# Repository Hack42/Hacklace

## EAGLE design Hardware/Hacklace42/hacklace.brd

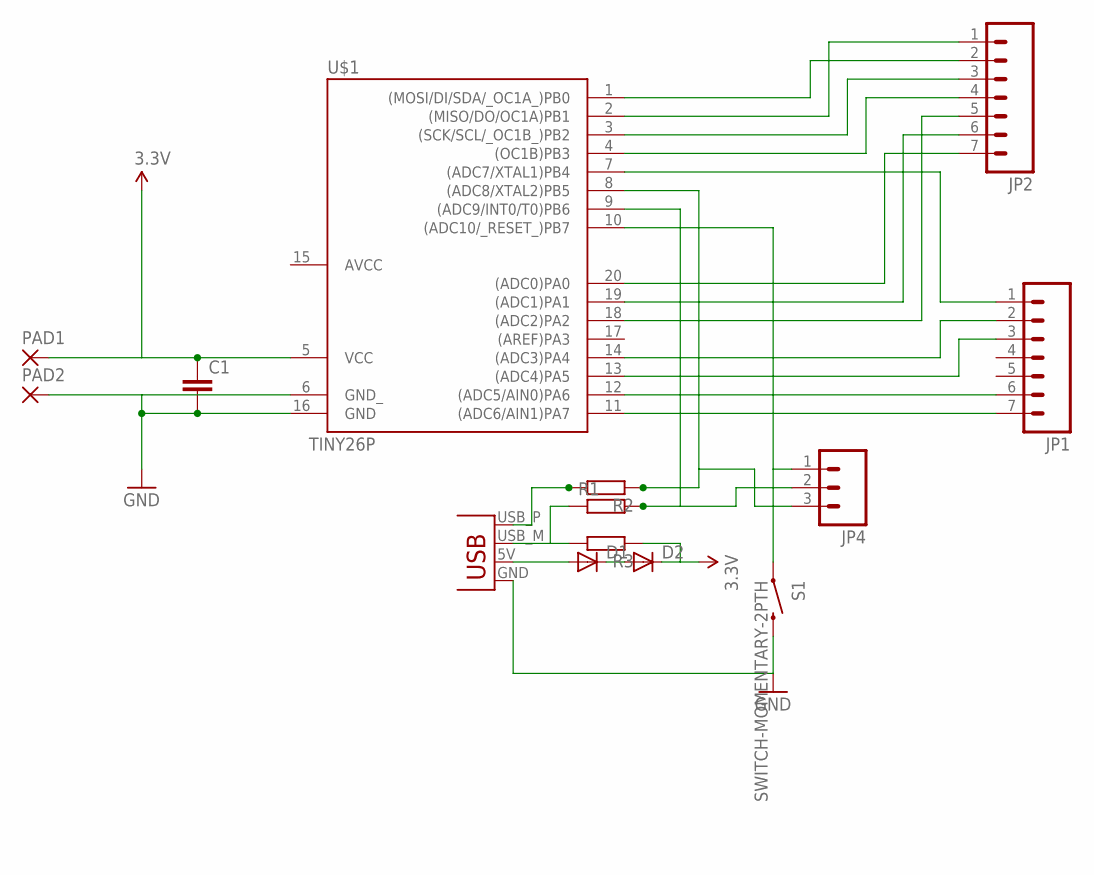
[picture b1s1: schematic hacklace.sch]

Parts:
C1: C-EU025-025X050; C025-025X050
D1, D2: DIODE-D-5; D-5
JP1, JP2: M07; 1X07
JP3: USBPCB; USB-A-PCB
JP4: M03PTH; 1X03
PAD1, PAD2: 1,6/0,8
R1, R2, R3: R-EU_0204/7; 0204/7
S1: SWITCH-MOMENTARY-2PTH; TACTILE-PTH
U$1: TINY26P; DIL20

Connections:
3.3V: C1.1, D2.C, PAD1.1, R3.1, U$1.5 (VCC)
AVCC: U$1.15 (AVCC)
GND: C1.2, JP3.GND, PAD2.1, S1.3 (2), U$1.6 (GND_), U$1.16 (GND)
unnamed: JP3.USB_M (D-), R1.1, R3.2
unnamed: JP4.1, S1.1, U$1.10 ((ADC10/_RESET_)PB7)
unnamed: JP1.2, U$1.14 ((ADC3)PA4)
unnamed: JP4.2, R1.2, U$1.9 ((ADC9/INT0/T0)PB6)
unnamed: JP4.3, R2.1, U$1.8 ((ADC8/XTAL2)PB5)
unnamed: JP2.6, U$1.19 ((ADC1)PA1)
unnamed: JP2.2, U$1.1 ((MOSI/DI/SDA/_OC1A_)PB0)
unnamed: D1.A, JP3.5V (VBUS)
unnamed: JP2.4, U$1.4 ((OC1B)PB3)
unnamed: JP2.3, U$1.3 ((SCK/SCL/_OC1B_)PB2)
unnamed: JP2.7, U$1.20 ((ADC0)PA0)
unnamed: JP1.6, U$1.12 ((ADC5/AIN0)PA6)
unnamed: JP2.5, U$1.18 ((ADC2)PA2)
unnamed: JP2.1, U$1.2 ((MISO/DO/OC1A)PB1)
unnamed: JP1.3, U$1.13 ((ADC4)PA5)
unnamed: JP1.7, U$1.11 ((ADC6/AIN1)PA7)
unnamed: JP3.USB_P (D+), R2.2
unnamed: JP1.1, U$1.7 ((ADC7/XTAL1)PB4)
unnamed: D1.C, D2.A

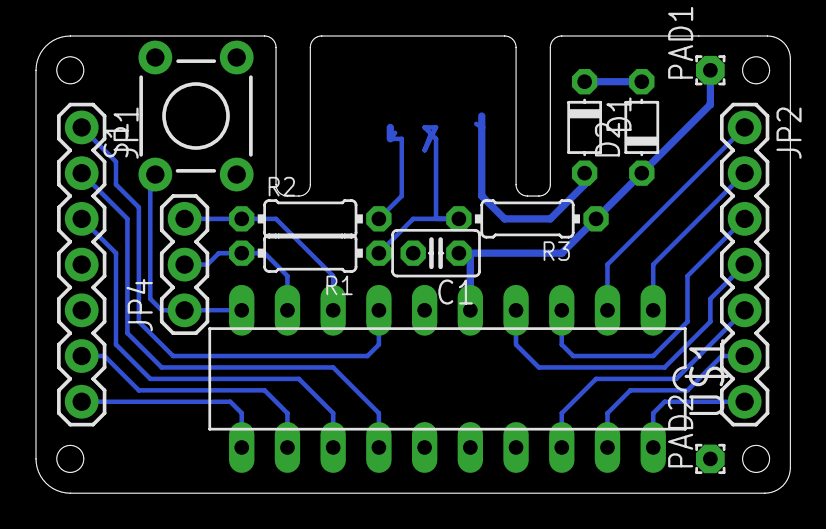
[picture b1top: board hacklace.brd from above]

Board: 1 copper layer, 41.9 x 25.4 mm, 14 parts (1 on the bottom side), 21 nets.

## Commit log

2013-09-16 Added Hacklace42 board and schema files
2013-09-16 Added png images of Hacklace42 board and schema.
2013-09-16 Resized image.
2013-09-18 Create display-matrix.lbr
    Eagle library with a couple of LED matrix parts

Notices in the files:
parts and their libraries:
SparkFun-Connectors: Licensing: CC v3.0 Share-Alike You are welcome to use this library for commercial purposes.
